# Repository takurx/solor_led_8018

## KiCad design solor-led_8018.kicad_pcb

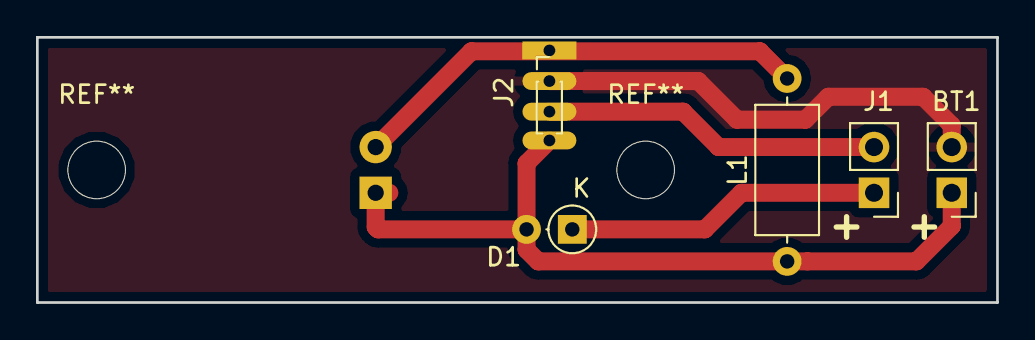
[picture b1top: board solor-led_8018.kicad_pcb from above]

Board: 2 copper layers, 53.3 x 14.7 mm, 6 parts (1 on the bottom side), 5 nets.

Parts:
BT1: Battery_Cell; PinHeader_1x02_P2.54mm_Vertical
D1: DIODE; D_DO-35_SOD27_P2.54mm_Vertical_AnodeUp
D2: LED; LED_D5.0mm
J1: Solar; PinHeader_1x02_P2.54mm_Vertical
J2: XY8018; PinHeader_1x04_P1.00mm_Vertical
L1: INDUCTOR; L_Axial_L7.0mm_D3.3mm_P10.16mm_Horizontal_Fastron_MICC

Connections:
GND: BT1.2, J2.2
unnamed: BT1.1, D1.2, D2.1, J2.4, L1.1
unnamed: D1.1, J1.1
unnamed: D2.2, J2.1, L1.2
unnamed: J1.2, J2.3

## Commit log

2019-03-11 screw point only one side
    screw point only one side.
    It will change both side.
2019-03-18 add screw point
    add screw point
